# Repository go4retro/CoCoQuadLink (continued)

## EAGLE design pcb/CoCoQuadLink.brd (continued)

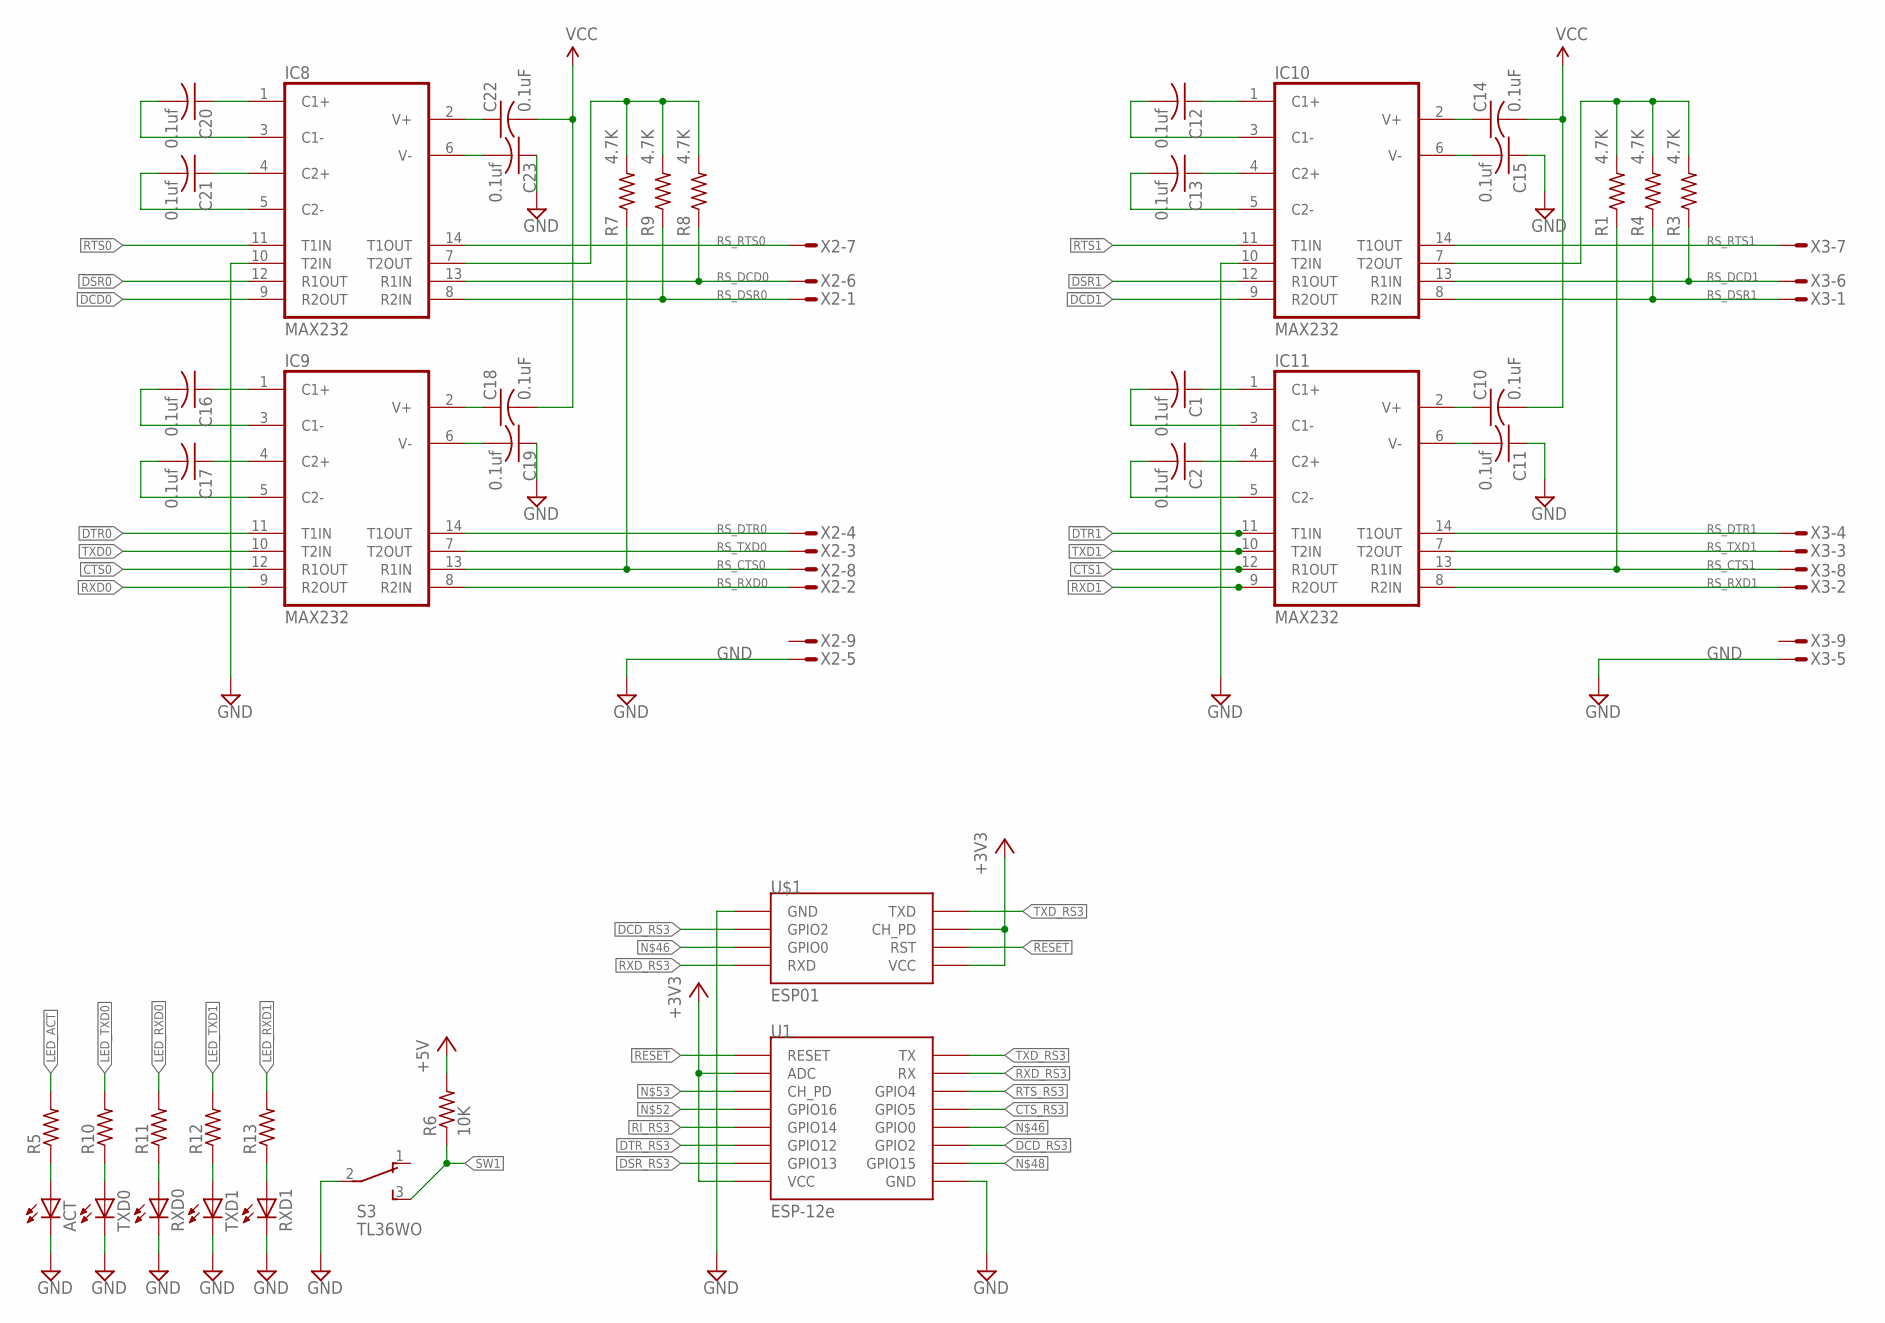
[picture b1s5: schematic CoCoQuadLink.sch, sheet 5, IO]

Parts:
ACT: LED3MM
C1, C2, C11, C12, C13, C15, C16, C17, C19, C20, C21, C23: 0.1uf; C0402
C10, C14, C18, C22: 0.1uF; C0402
IC8, IC9, IC10, IC11: MAX232; SO16
R1, R3, R4, R7, R8, R9: 4.7K; R1206
R5, R10, R11, R12, R13: R-US_R0402; R0402
R6: 10K; R0402
RXD0, RXD1: LED3MM
S3: TL36WO; TL3XWO
TXD0, TXD1: LED3MM
U1: ESP-12e; ESP12
U$1: ESP01
X2, X3: M09DS; M09D

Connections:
!CTS0: IC9.12 (R1OUT); also elsewhere on the board
!CTS1: IC11.12 (R1OUT); also elsewhere on the board
!DCD0: IC8.9 (R2OUT); also elsewhere on the board
!DCD1: IC10.9 (R2OUT); also elsewhere on the board
!DSR0: IC8.12 (R1OUT); also elsewhere on the board
!DSR1: IC10.12 (R1OUT); also elsewhere on the board
!DTR0: IC9.11 (T1IN); also elsewhere on the board
!DTR1: IC11.11 (T1IN); also elsewhere on the board
!RESET: U1.RESET, U$1.RST; also elsewhere on the board
!RTS0: IC8.11 (T1IN); also elsewhere on the board
!RTS1: IC10.11 (T1IN); also elsewhere on the board
+3V3: U1.ADC, U1.VCC, U$1.CH_PD, U$1.VCC; also elsewhere on the board
CTS_RS3: U1.GPIO5; also elsewhere on the board
DCD_RS3: U1.GPIO2, U$1.GPIO2; also elsewhere on the board
DSR_RS3: U1.GPIO13; also elsewhere on the board
DTR_RS3: U1.GPIO12; also elsewhere on the board
GND: ACT.K (C), C11.1, C15.1, C19.1, C23.1, IC8.10 (T2IN), IC8.15 (GND), IC9.15 (GND), IC10.10 (T2IN), IC10.15 (GND), IC11.15 (GND), RXD0.K (C), RXD1.K (C), S3.2, TXD0.K (C), TXD1.K (C), U1.GND, U$1.GND, X2.5, X3.5; also elsewhere on the board
LED_ACT: R5.2; also elsewhere on the board
LED_RXD0: R11.2; also elsewhere on the board
LED_RXD1: R13.2; also elsewhere on the board
LED_TXD0: R10.2; also elsewhere on the board
LED_TXD1: R12.2; also elsewhere on the board
unnamed: ACT.A, R5.1
unnamed: C16.1, IC9.1 (C1+)
unnamed: C16.2, IC9.3 (C1-)
unnamed: C17.1, IC9.4 (C2+)
unnamed: C17.2, IC9.5 (C2-)
unnamed: IC10.7 (T2OUT), R1.2, R3.2, R4.2
unnamed: C1.1, IC11.1 (C1+)
unnamed: C18.1, IC9.2 (V+)
unnamed: C19.2, IC9.6 (V-)
unnamed: C20.1, IC8.1 (C1+)
unnamed: C1.2, IC11.3 (C1-)
unnamed: C2.1, IC11.4 (C2+)
unnamed: C2.2, IC11.5 (C2-)
unnamed: C10.1, IC11.2 (V+)
unnamed: C11.2, IC11.6 (V-)
unnamed: C12.1, IC10.1 (C1+)
unnamed: C12.2, IC10.3 (C1-)
unnamed: C13.1, IC10.4 (C2+)
unnamed: C20.2, IC8.3 (C1-)
unnamed: C21.1, IC8.4 (C2+)
unnamed: C21.2, IC8.5 (C2-)
unnamed: C22.1, IC8.2 (V+)
unnamed: C23.2, IC8.6 (V-)
unnamed: IC8.7 (T2OUT), R7.2, R8.2, R9.2
unnamed: C13.2, IC10.5 (C2-)
unnamed: C14.1, IC10.2 (V+)
unnamed: C15.2, IC10.6 (V-)
unnamed: R10.1, TXD0.A
unnamed: R11.1, RXD0.A
unnamed: R12.1, TXD1.A
unnamed: R13.1, RXD1.A
unnamed 143: U1.GPIO0, U$1.GPIO0; also elsewhere on the board
unnamed 144: U1.GPIO15; also elsewhere on the board
unnamed 145: U1.GPIO16; also elsewhere on the board
unnamed 146: U1.CH_PD; also elsewhere on the board
RI_RS3: U1.GPIO14; also elsewhere on the board
RS_CTS0: IC9.13 (R1IN), R7.1, X2.8
RS_CTS1: IC11.13 (R1IN), R1.1, X3.8
RS_DCD0: IC8.13 (R1IN), R8.1, X2.6
RS_DCD1: IC10.13 (R1IN), R3.1, X3.6
RS_DSR0: IC8.8 (R2IN), R9.1, X2.1
RS_DSR1: IC10.8 (R2IN), R4.1, X3.1
RS_DTR0: IC9.14 (T1OUT), X2.4
RS_DTR1: IC11.14 (T1OUT), X3.4
RS_RTS0: IC8.14 (T1OUT), X2.7
RS_RTS1: IC10.14 (T1OUT), X3.7
RS_RXD0: IC9.8 (R2IN), X2.2
RS_RXD1: IC11.8 (R2IN), X3.2
RS_TXD0: IC9.7 (T2OUT), X2.3
RS_TXD1: IC11.7 (T2OUT), X3.3
RTS_RS3: U1.GPIO4; also elsewhere on the board
RXD0: IC9.9 (R2OUT); also elsewhere on the board
RXD1: IC11.9 (R2OUT); also elsewhere on the board
RXD_RS3: U1.RX, U$1.RX (RXD); also elsewhere on the board
SW1: R6.1, S3.3 (S); also elsewhere on the board
TXD0: IC9.10 (T2IN); also elsewhere on the board
TXD1: IC11.10 (T2IN); also elsewhere on the board
TXD_RS3: U1.TX, U$1.TX (TXD); also elsewhere on the board
VCC: C10.2, C14.2, C18.2, C22.2, IC8.16 (VCC), IC9.16 (VCC), IC10.16 (VCC), IC11.16 (VCC), R6.2; also elsewhere on the board

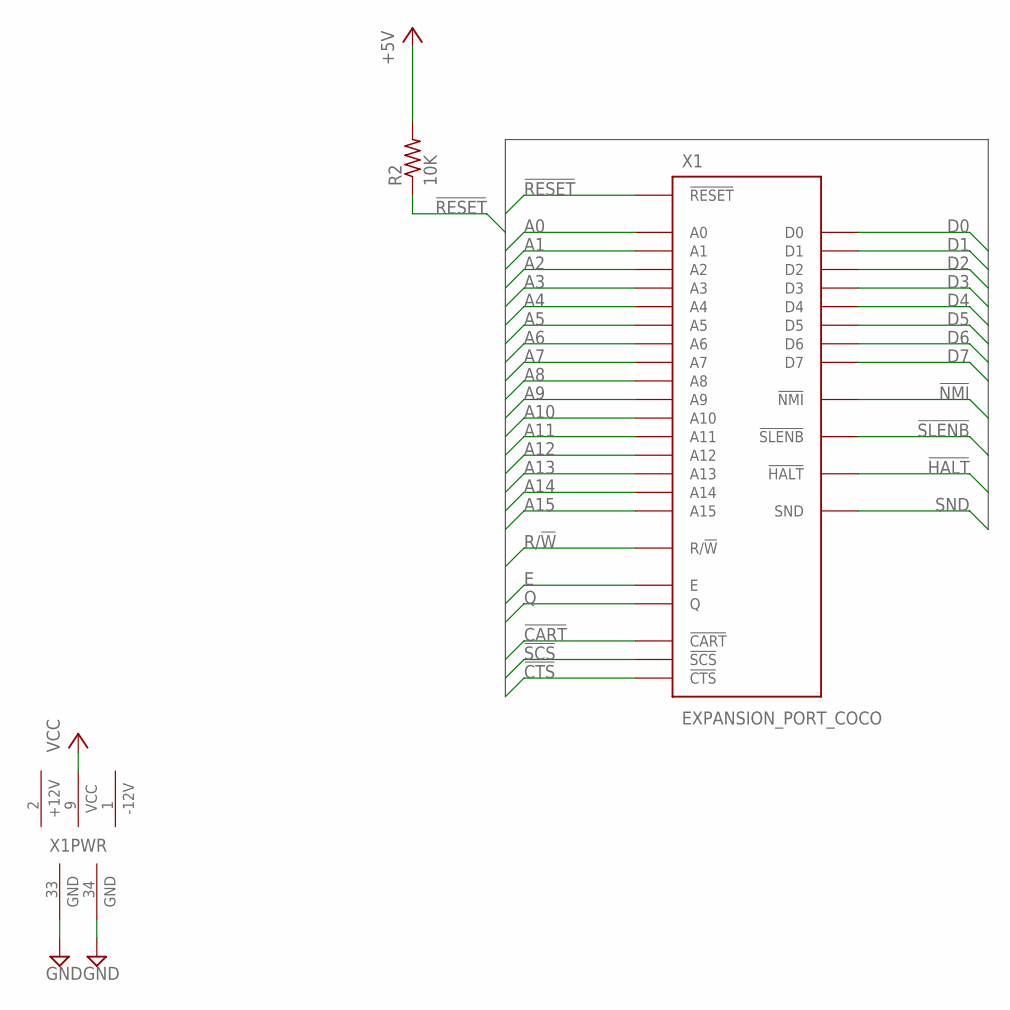
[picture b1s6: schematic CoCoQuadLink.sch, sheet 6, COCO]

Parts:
R2: 10K; R0402
X1: EXPANSION_PORT_COCO; MA20-2

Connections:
!CART: X1.8 (!CART); also elsewhere on the board
!CTS: X1.32 (!CTS); also elsewhere on the board
!HALT: X1.3 (!HALT)
!NMI: X1.4 (!NMI); also elsewhere on the board
!RESET: R2.1, X1.5 (!RESET); also elsewhere on the board
!SCS: X1.36 (!SCS); also elsewhere on the board
!SLENB: X1.40 (!SLENB); also elsewhere on the board
+12V: X1.2 (+12V)
-12V: X1.1 (-12V)
A0: X1.19 (A0); also elsewhere on the board
A1: X1.20 (A1); also elsewhere on the board
A2: X1.21 (A2); also elsewhere on the board
A3: X1.22 (A3); also elsewhere on the board
A4: X1.23 (A4); also elsewhere on the board
A5: X1.24 (A5); also elsewhere on the board
A6: X1.25 (A6); also elsewhere on the board
A7: X1.26 (A7); also elsewhere on the board
A8: X1.27 (A8); also elsewhere on the board
A9: X1.28 (A9); also elsewhere on the board
A10: X1.29 (A10); also elsewhere on the board
A11: X1.30 (A11); also elsewhere on the board
A12: X1.31 (A12); also elsewhere on the board
A13: X1.37 (A13); also elsewhere on the board
A14: X1.38 (A14); also elsewhere on the board
A15: X1.39 (A15); also elsewhere on the board
D0: X1.10 (D0); also elsewhere on the board
D1: X1.11 (D1); also elsewhere on the board
D2: X1.12 (D2); also elsewhere on the board
D3: X1.13 (D3); also elsewhere on the board
D4: X1.14 (D4); also elsewhere on the board
D5: X1.15 (D5); also elsewhere on the board
D6: X1.16 (D6); also elsewhere on the board
D7: X1.17 (D7); also elsewhere on the board
E: X1.6 (E); also elsewhere on the board
GND: X1.33 (GND), X1.34 (GND); also elsewhere on the board
Q: X1.7 (Q); also elsewhere on the board
R/!W: X1.18 (R/!W); also elsewhere on the board
SND: X1.35 (SND)
VCC: R2.2, X1.9 (VCC); also elsewhere on the board

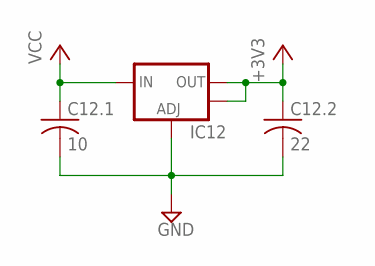
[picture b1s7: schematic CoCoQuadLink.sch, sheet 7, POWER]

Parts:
C12.1: 10; C0805
C12.2: 22; C0805
IC12: V_REG_LM1117SOT223; SOT223

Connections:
+3V3: C12.2.1, IC12.2 (OUT), IC12.4 (OUT); also elsewhere on the board
GND: C12.1.2, C12.2.2, IC12.1 (ADJ); also elsewhere on the board
VCC: C12.1.1, IC12.3 (IN); also elsewhere on the board

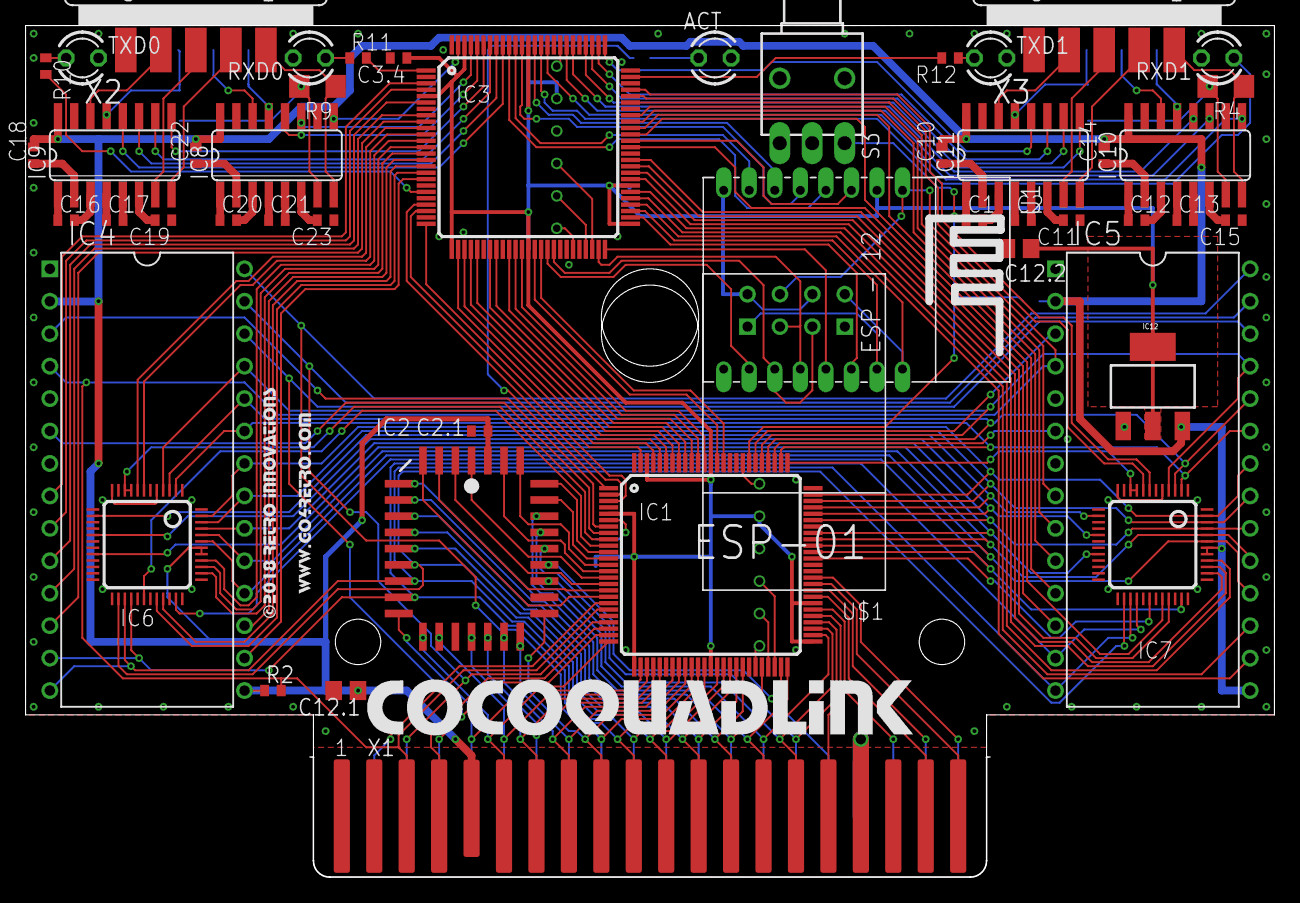
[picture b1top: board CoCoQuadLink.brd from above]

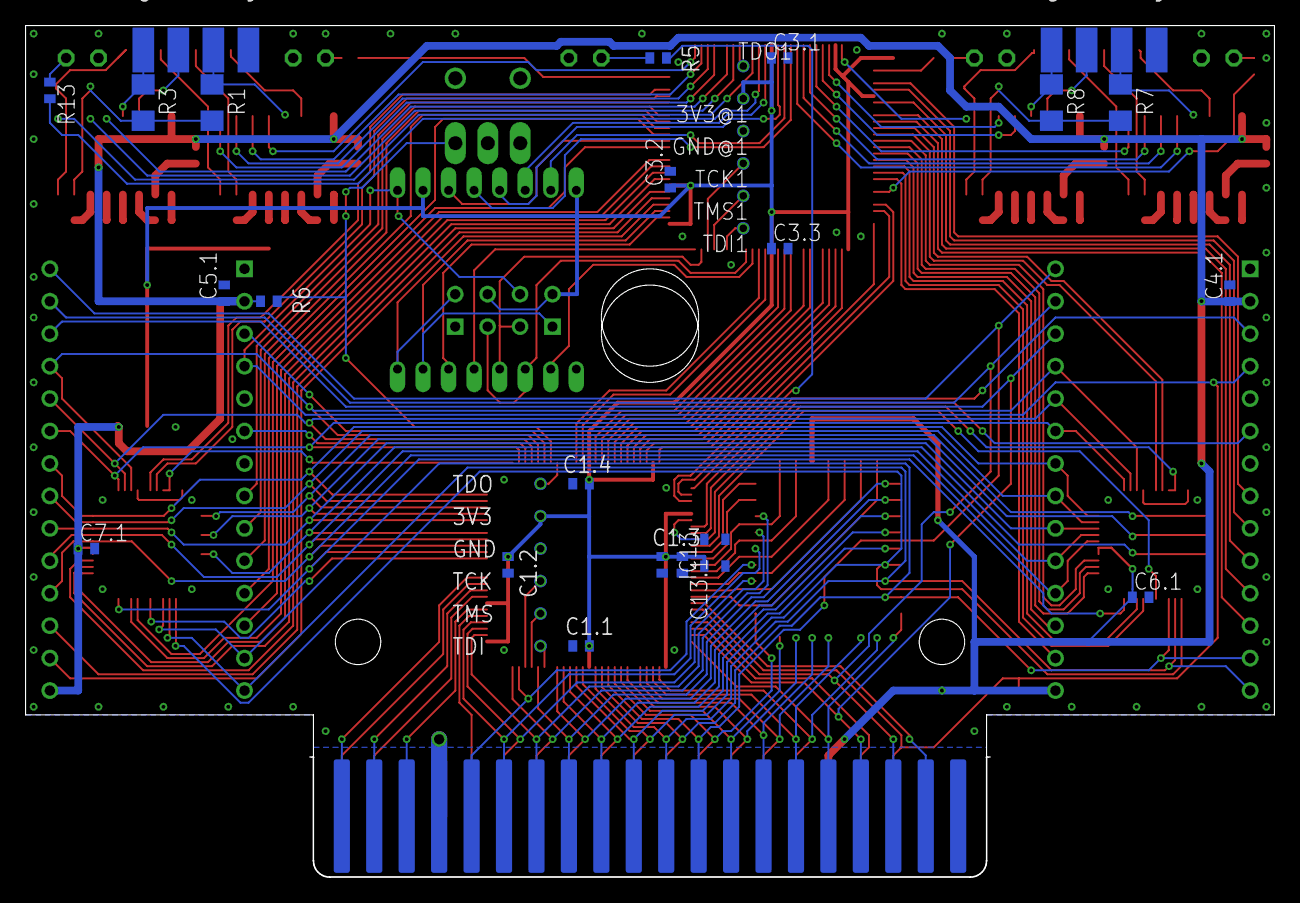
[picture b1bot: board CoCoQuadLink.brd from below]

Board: 2 copper layers, 97.8 x 66.7 mm, 82 parts (32 on the bottom side), 194 nets.

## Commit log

2019-03-21 Refreshed PCB
